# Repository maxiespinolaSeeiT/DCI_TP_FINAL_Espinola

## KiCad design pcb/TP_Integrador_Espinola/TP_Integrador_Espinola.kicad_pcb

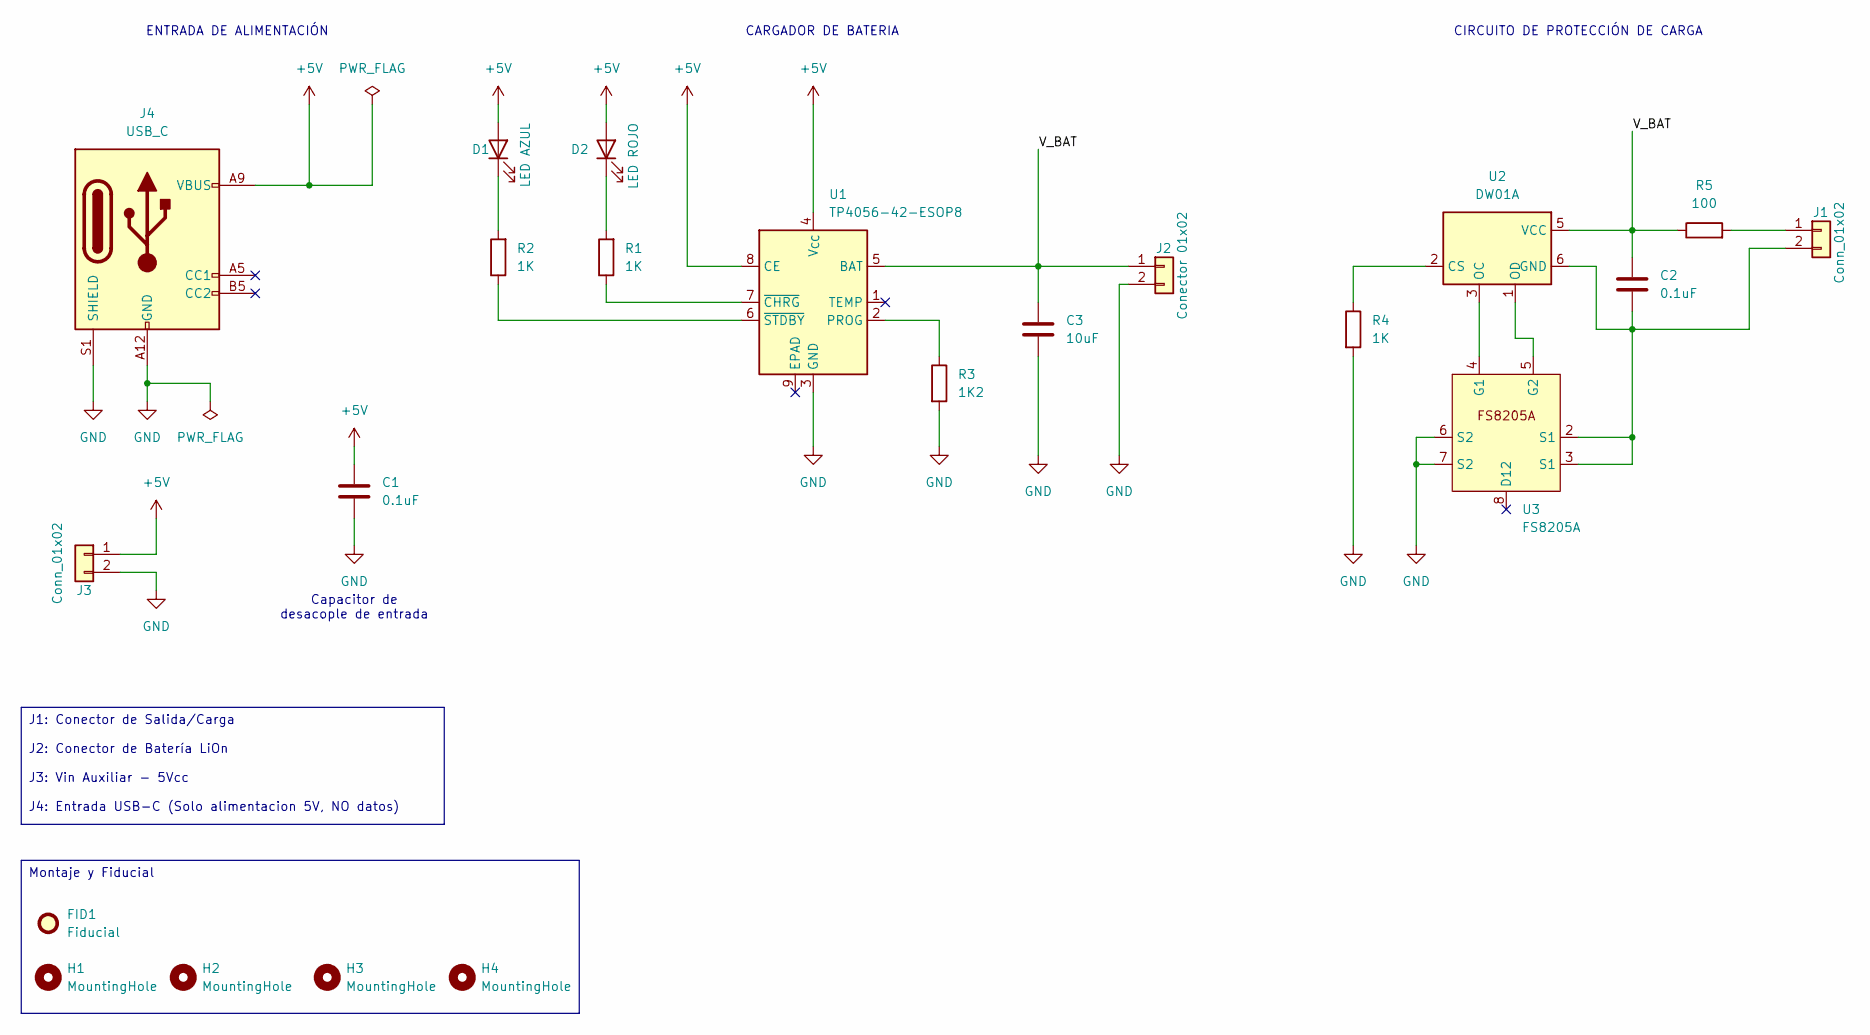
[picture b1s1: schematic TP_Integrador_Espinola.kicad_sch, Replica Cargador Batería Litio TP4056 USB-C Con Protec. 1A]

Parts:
C1, C2: 0.1uF; C_0805_2012Metric; MPN GRM21BR71H104KA01L
C3: 10uF; CP_Elec_5x5.3; MPN EEE-FK1A100P
D1: LED AZUL; LED_0805_2012Metric; MPN LTST-C170TBKT
D2: LED ROJO; LED_0805_2012Metric; MPN LTST-C170KRKT
FID1: Fiducial; Fiducial_1.5mm_Mask3mm; MPN N/A
H1, H2, H3, H4: MountingHole; MountingHole_2.2mm_M2_Pad_TopBottom; MPN N/A
J1, J3: Conn_01x02; TerminalBlock_Phoenix_MKDS-3-2-5.08_1x02_P5.08mm_Horizontal; MPN 1725656
J2: Conector 01x02; TerminalBlock_Phoenix_MKDS-3-2-5.08_1x02_P5.08mm_Horizontal; MPN 1725656
J4: USB_C; USB_C_Receptacle_GCT_USB4125-xx-x-0190_6P_TopMnt_Horizontal; MPN USB4125-GF-A-0190
R1, R2, R4: 1K; R_0805_2012Metric_Pad1.20x1.40mm_HandSolder; MPN RC0805FR-071KL
R3: 1K2; R_0805_2012Metric_Pad1.20x1.40mm_HandSolder; MPN RC0805FR-071K2L
R5: 100; R_0805_2012Metric_Pad1.20x1.40mm_HandSolder; MPN RC0805FR-07100RL
U1: TP4056-42-ESOP8; SOIC-8-1EP_3.9x4.9mm_P1.27mm_EP2.29x3mm_ThermalVias; MPN TP4056-42-ESOP8
U2: DW01A; SOT-23-6; MPN DW01A
U3: FS8205A; TSSOP-8_4.4x3mm_P0.65mm; MPN FS8205A

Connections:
+5V: C1.1, D1.2 (A), D2.2 (A), J3.1, J4.A9 (VBUS), J4.B9 (VBUS), U1.4 (V_{CC}), U1.8 (CE)
/V_BAT: C2.1, C3.1, J2.1, R5.1, U1.5 (BAT), U2.5 (VCC)
GND: C1.2, C3.2, J2.2, J3.2, J4.A12 (GND), J4.B12 (GND), J4.S1 (SHIELD), R3.2, R4.2, U1.3 (GND), U3.6 (S2), U3.7 (S2)
unnamed: D1.1 (K), R2.2
unnamed: D2.1 (K), R1.2
unnamed: J1.1, R5.2
unnamed: C2.2, J1.2, U2.6 (GND), U3.2 (S1), U3.3 (S1)
unnamed: R3.1, U1.2 (PROG)
unnamed: R1.1, U1.7 (~CHRG)
unnamed: R2.1, U1.6 (~STDBY)
unnamed: R4.1, U2.2 (CS)
unnamed: U2.3 (OC), U3.4 (G1)
unnamed: U2.1 (OD), U3.5 (G2)

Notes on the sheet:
CIRCUITO DE PROTECCIÓN DE CARGA
Capacitor de desacople de entrada
CARGADOR DE BATERIA
ENTRADA DE ALIMENTACIÓN
J1: Conector de Salida/Carga J2: Conector de Batería LiOn J3: Vin Auxiliar - 5Vcc J4: Entrada USB-C (Solo alimentacion 5V, NO datos)
Montaje y Fiducial

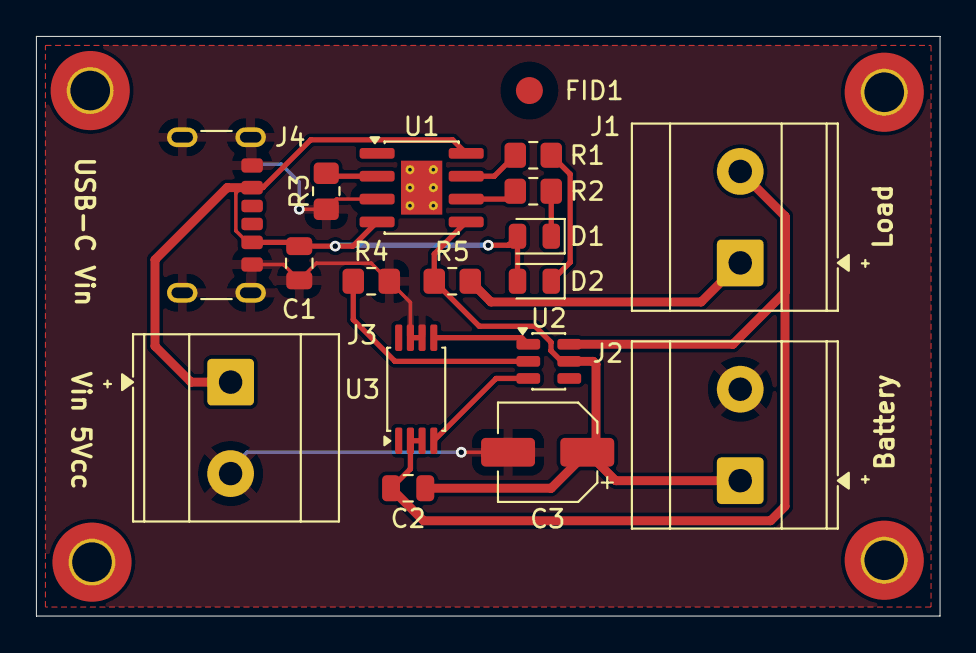
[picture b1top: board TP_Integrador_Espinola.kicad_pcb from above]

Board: 2 copper layers, 50.2 x 32.2 mm, 22 parts (0 on the bottom side), 13 nets.

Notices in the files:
pcb/TP_Integrador_Espinola/TP_Integrador_Espinola.kicad_pcb:
Lic: CERN Open Hardware Licence Version 2 – Strongly Reciprocal (CERN-OHL-S-2.0)
